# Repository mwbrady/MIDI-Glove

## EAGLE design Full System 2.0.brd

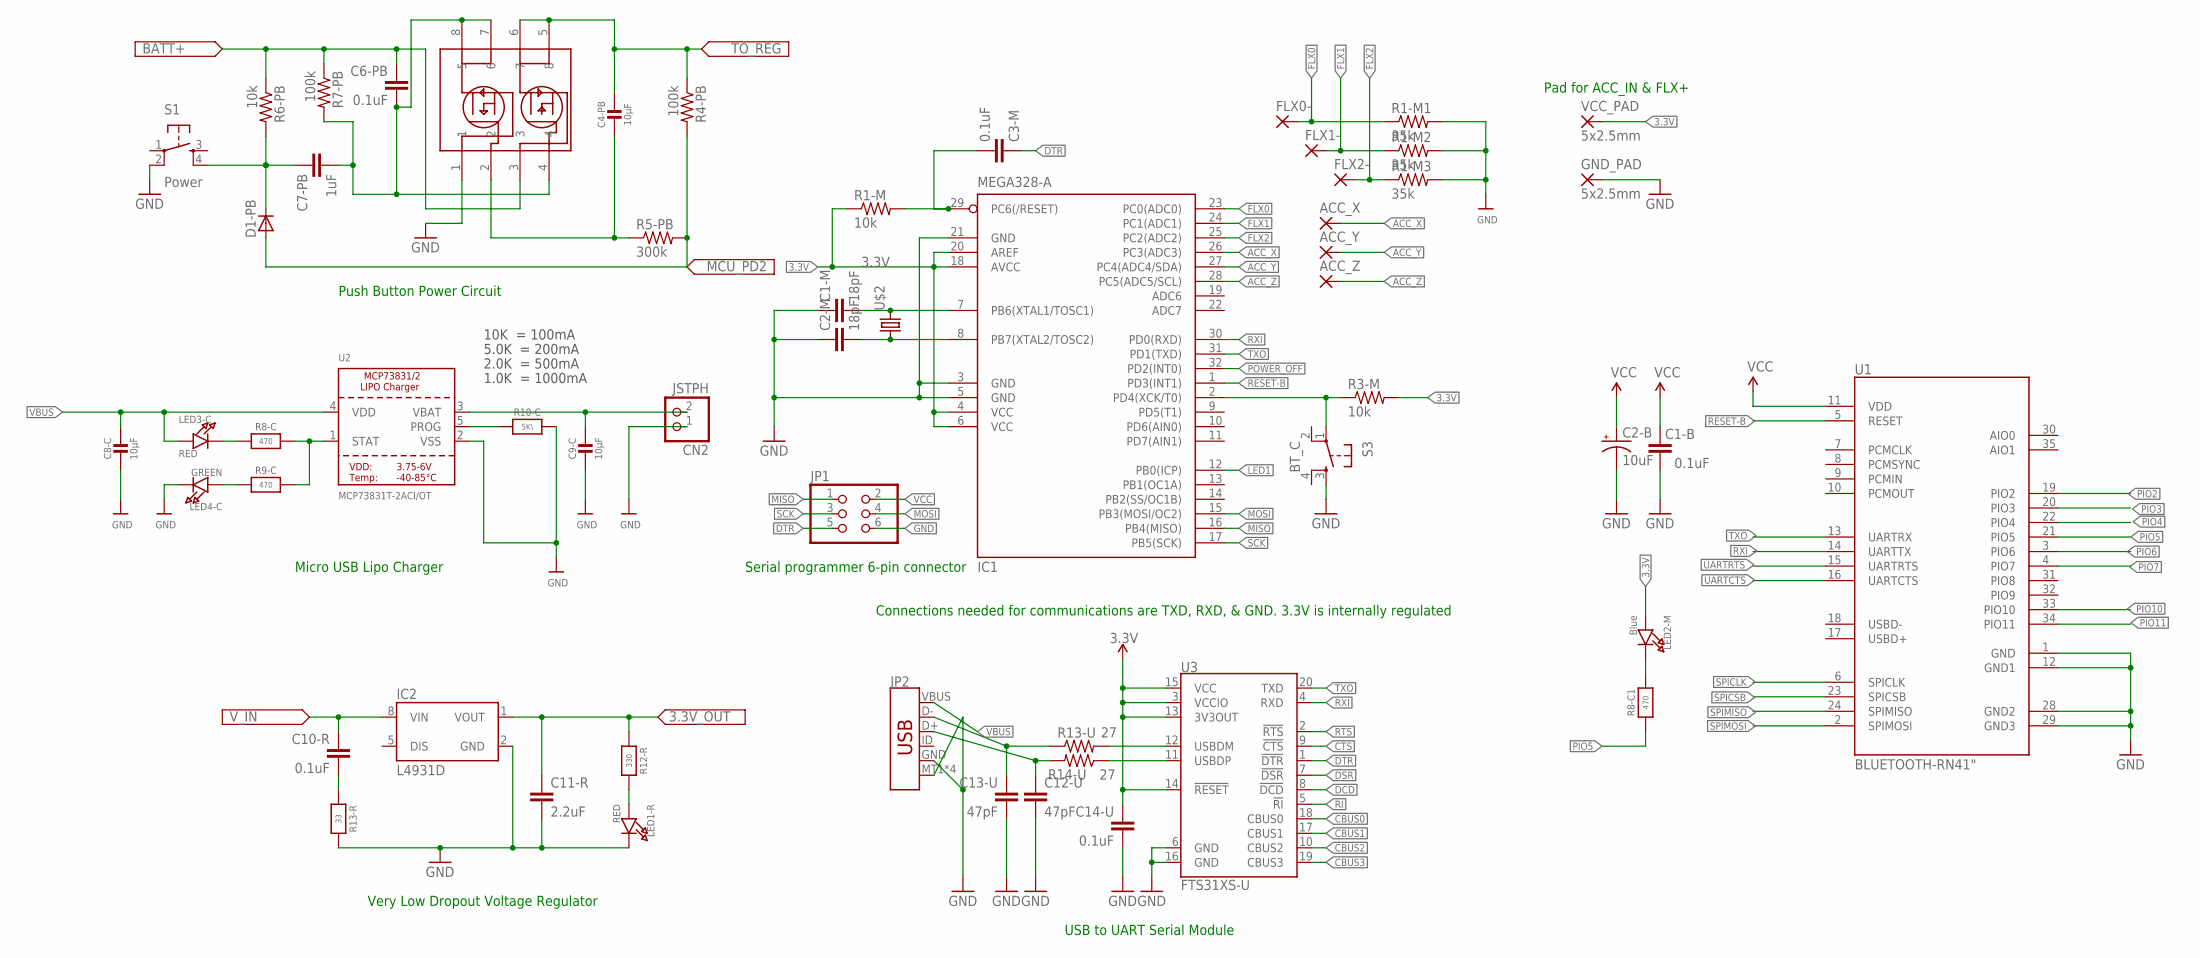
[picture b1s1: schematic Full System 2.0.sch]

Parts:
ACC_X: 1,6/0,8
ACC_Y: 1,6/0,8
ACC_Z: 1,6/0,8
C1-B, C3-M, C6-PB, C10-R, C14-U: 0.1uF; 0603-CAP
C1-M, C2-M: 18pF; C0603
C2-B: 10uF; EIA3216
C4-PB, C8-C, C9-C: 10µF; 0805-NO
C7-PB: 1uF; 0603-CAP
C11-R: 2.2uF; 0603-CAP
C12-U, C13-U: 47pF; 0603-CAP
CN2: JSTPH; JSTPH2
D1-PB: D-A1-C3; SOT23
FLX0-, FLX1-, FLX2-: 1,6/0,8
GND_PAD: 5x2.5mm; 5-2,5
IC1: MEGA328-A; TQFP32-08
IC2: L4931D; SO08
JP1: PINHD-2X3; 2X03
JP2: USB_MICRO-B_SMT; USB-MICROB
LED1-R, LED3-C: RED; CHIPLED_0805_NOOUTLINE
LED2-M: Blue; CHIPLED_0805_NOOUTLINE
LED4-C: GREEN; CHIPLED_0805_NOOUTLINE
R1-M, R3-M, R6-PB: 10k; R0805
R1-M1, R1-M2, R1-M3: 35k; R0805
R4-PB, R7-PB: 100k; R0805
R5-PB: 300k; R0805
R8-C, R8-C1, R9-C: 470; 0805-NO
R10-C: 5K\; 0805-NO
R12-R: 330; 0805-NO
R13-R: 33; 0805-NO
R13-U, R14-U: 27; 0603-RES
S1: Power; TACTILE_SWITCH_SMD
S3: BT_C; TACTILE_SWITCH_SMD
U1: BLUETOOTH-RN41"; RN41
U2: MCP73831T-2ACI/OT; SOT23-5
U3: FTS31XS-U; SSOP20_L
U$2: CRYSTAL
U$8: IRF7319PBF
VCC_PAD: 5x2.5mm; 5-2,5

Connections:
3.3V: C1-B.1, C2-B.A (+), C11-R.1, C14-U.1, IC1.4 (VCC), IC1.6 (VCC), IC1.18 (AVCC), IC1.20 (AREF), IC2.1 (VOUT), LED2-M.A, R1-M.1, R3-M.2, R12-R.1, U1.11 (VDD), U3.3 (VCCIO), U3.13 (3V3OUT), U3.14 (!RESET), U3.15 (VCC), VCC_PAD.1
ACC_X: ACC_X.1, IC1.26 (PC3(ADC3))
ACC_Y: ACC_Y.1, IC1.27 (PC4(ADC4/SDA))
ACC_Z: ACC_Z.1, IC1.28 (PC5(ADC5/SCL))
CBUS0: U3.18 (CBUS0)
CBUS3: U3.19 (CBUS3)
CTS: U3.9 (!CTS)
DCD: U3.8 (!DCD)
DSR: U3.7 (!DSR)
DTR: C3-M.1, JP1.5, U3.1 (!DTR)
FLX0: FLX0-.1, IC1.23 (PC0(ADC0)), R1-M1.1
FLX1: FLX1-.1, IC1.24 (PC1(ADC1)), R1-M2.1
FLX2: FLX2-.1, IC1.25 (PC2(ADC2)), R1-M3.1
GND: C1-B.2, C1-M.1, C2-B.C (-), C2-M.1, C8-C.2, C9-C.2, C11-R.2, C12-U.2, C13-U.2, C14-U.2, CN2.1, GND_PAD.1, IC1.3 (GND), IC1.5 (GND), IC1.21 (GND), IC2.2 (GND), JP1.6, JP2.GND, JP2.MT1 (SHIELD), JP2.MT2 (SHIELD), JP2.P$1 (SHIELD), JP2.P$2 (SHIELD), LED1-R.C, LED4-C.C, R1-M1.2, R1-M2.2, R1-M3.2, R10-C.2, R13-R.2, S1.2, S3.3, U1.1 (GND), U1.12 (GND1), U1.28 (GND2), U1.29 (GND3), U2.2 (VSS), U3.6 (GND), U3.16 (GND), U$8.1
LED1: IC1.12 (PB0(ICP))
MISO: IC1.16 (PB4(MISO)), JP1.1
MOSI: IC1.15 (PB3(MOSI/OC2)), JP1.4
unnamed: R13-U.2, U3.12 (USBDM)
unnamed: C1-M.2, IC1.7 (PB6(XTAL1/TOSC1)), U$2.P$2 (2)
unnamed: C2-M.2, IC1.8 (PB7(XTAL2/TOSC2)), U$2.P$1 (1)
unnamed: C6-PB.2, C7-PB.2, R7-PB.2, U$8.4, U$8.7 (6), U$8.8 (5)
unnamed: C7-PB.1, D1-PB.3 (C), R6-PB.2, S1.4
unnamed: IC1.2 (PD4(XCK/T0)), R3-M.1, S3.1
unnamed: LED1-R.A, R12-R.2
unnamed: C10-R.2, R13-R.1
unnamed: C4-PB.2, R5-PB.1, U$8.2
unnamed: LED2-M.C, R8-C1.2
unnamed: R14-U.1, U3.11 (USBDP)
unnamed: C12-U.1, JP2.D+, R14-U.2
unnamed: LED3-C.C, R8-C.1
unnamed: R8-C.2, R9-C.2, U2.1 (STAT)
unnamed: R10-C.1, U2.5 (PROG)
unnamed: LED4-C.A, R9-C.1
unnamed: C13-U.1, JP2.D-, R13-U.1
PIO2: U1.19 (PIO2)
PIO3: U1.20 (PIO3)
PIO4: U1.22 (PIO4)
PIO5: R8-C1.1, U1.21 (PIO5)
PIO6: U1.3 (PIO6)
PIO7: U1.4 (PIO7)
PIO10: U1.33 (PIO10)
PIO11: U1.34 (PIO11)
POWER_OFF: D1-PB.1 (A), IC1.32 (PD2(INT0)), R4-PB.2, R5-PB.2
RESET: C3-M.2, IC1.29 (PC6(/RESET)), R1-M.2
RESET-B: IC1.1 (PD3(INT1)), U1.5 (RESET)
RI: U3.5 (!RI)
RTS: U3.2 (!RTS)
RXI: IC1.30 (PD0(RXD)), U1.14 (UARTTX), U3.4 (RXD)
SCK: IC1.17 (PB5(SCK)), JP1.3
SPICLK: U1.6 (SPICLK)
SPICSB: U1.23 (SPICSB)
SPIMISO: U1.24 (SPIMISO)
SPIMOSI: U1.2 (SPIMOSI)
TXO: IC1.31 (PD1(TXD)), U1.13 (UARTRX), U3.20 (TXD)
UARTCTS: U1.16 (UARTCTS)
UARTRTS: U1.15 (UARTRTS)
VBAT: C6-PB.1, C9-C.1, CN2.2, R6-PB.1, R7-PB.1, U2.3 (VBAT), U$8.3
VBUS: C8-C.1, JP2.VBUS, LED3-C.A, U2.4 (VDD)
VCC: JP1.2
V_IN: C4-PB.1, C10-R.1, IC2.8 (VIN), R4-PB.1, U$8.5 (8), U$8.6 (7)

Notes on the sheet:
Serial programmer 6-pin connector
Pad for ACC_IN & FLX+
Connections needed for communications are TXD, RXD, & GND. 3.3V is internally regulated
10K = 100mA
5.0K = 200mA
2.0K = 500mA
1.0K = 1000mA
USB to UART Serial Module
Very Low Dropout Voltage Regulator
Micro USB Lipo Charger
Push Button Power Circuit

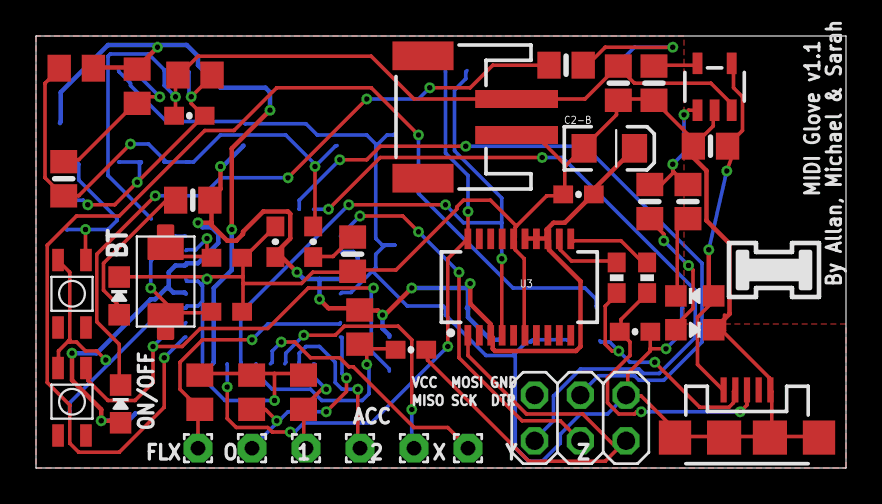
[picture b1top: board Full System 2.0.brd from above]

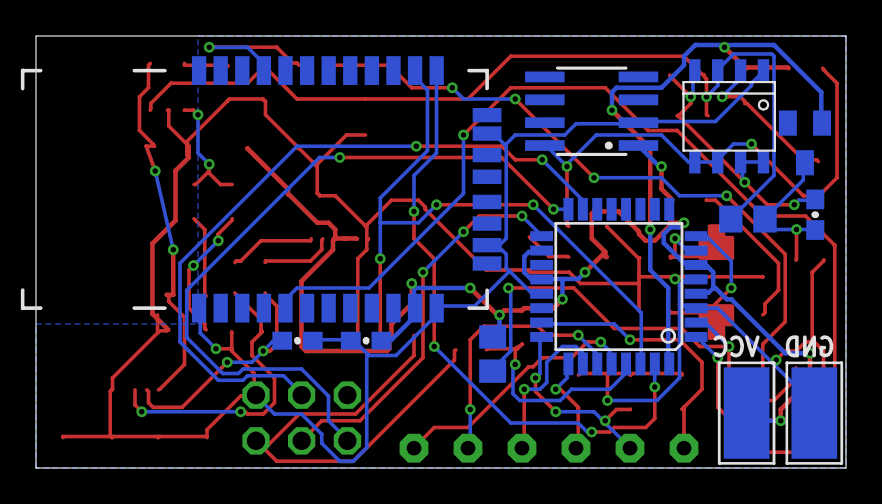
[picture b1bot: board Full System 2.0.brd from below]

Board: 2 copper layers, 45.0 x 24.0 mm, 57 parts (12 on the bottom side), 38 nets.

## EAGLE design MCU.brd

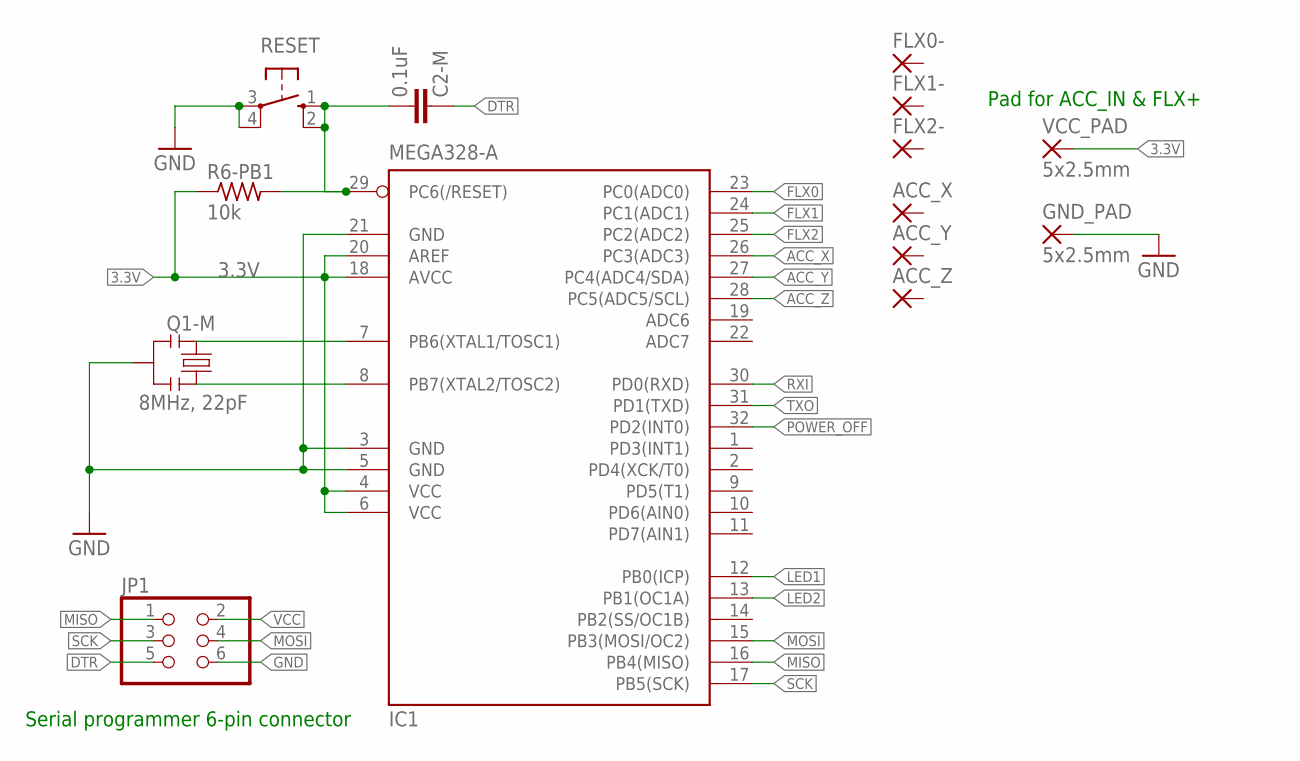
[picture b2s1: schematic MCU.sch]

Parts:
ACC_X: 1,6/0,8
ACC_Y: 1,6/0,8
ACC_Z: 1,6/0,8
C2-M: 0.1uF; 0603-CAP
FLX0-, FLX1-, FLX2-: 1,6/0,8
GND_PAD: 5x2.5mm; 5-2,5
IC1: MEGA328-A; TQFP32-08
JP1: PINHD-2X3; 2X03
Q1-M: 8MHz, 22pF; RESONATOR-SMD-1:1
R6-PB1: 10k; R0805
RESET: 10-XX; B3F-10XX
VCC_PAD: 5x2.5mm; 5-2,5

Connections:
3.3V: IC1.4 (VCC), IC1.6 (VCC), IC1.18 (AVCC), IC1.20 (AREF), R6-PB1.1, VCC_PAD.1
ACC_X: IC1.26 (PC3(ADC3))
ACC_Y: IC1.27 (PC4(ADC4/SDA))
ACC_Z: IC1.28 (PC5(ADC5/SCL))
DTR: C2-M.2, JP1.5
FLX0: IC1.23 (PC0(ADC0))
FLX2: IC1.25 (PC2(ADC2))
FLX!: IC1.24 (PC1(ADC1))
GND: GND_PAD.1, IC1.3 (GND), IC1.5 (GND), IC1.21 (GND), JP1.6, Q1-M.2, RESET.3, RESET.4 (P1)
MISO: IC1.16 (PB4(MISO)), JP1.1
MOSI: IC1.15 (PB3(MOSI/OC2)), JP1.4
unnamed: C2-M.1, IC1.29 (PC6(/RESET)), R6-PB1.2, RESET.1 (S), RESET.2 (S1)
unnamed: IC1.7 (PB6(XTAL1/TOSC1)), Q1-M.1
unnamed: IC1.8 (PB7(XTAL2/TOSC2)), Q1-M.3
POWER_OFF: IC1.32 (PD2(INT0))
RXI: IC1.30 (PD0(RXD))
SCK: IC1.17 (PB5(SCK)), JP1.3
TXO: IC1.31 (PD1(TXD))
VCC: JP1.2

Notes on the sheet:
Serial programmer 6-pin connector
Pad for ACC_IN & FLX+

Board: 2 copper layers, 14 parts (0 on the bottom side), 9 nets, no tracks yet.

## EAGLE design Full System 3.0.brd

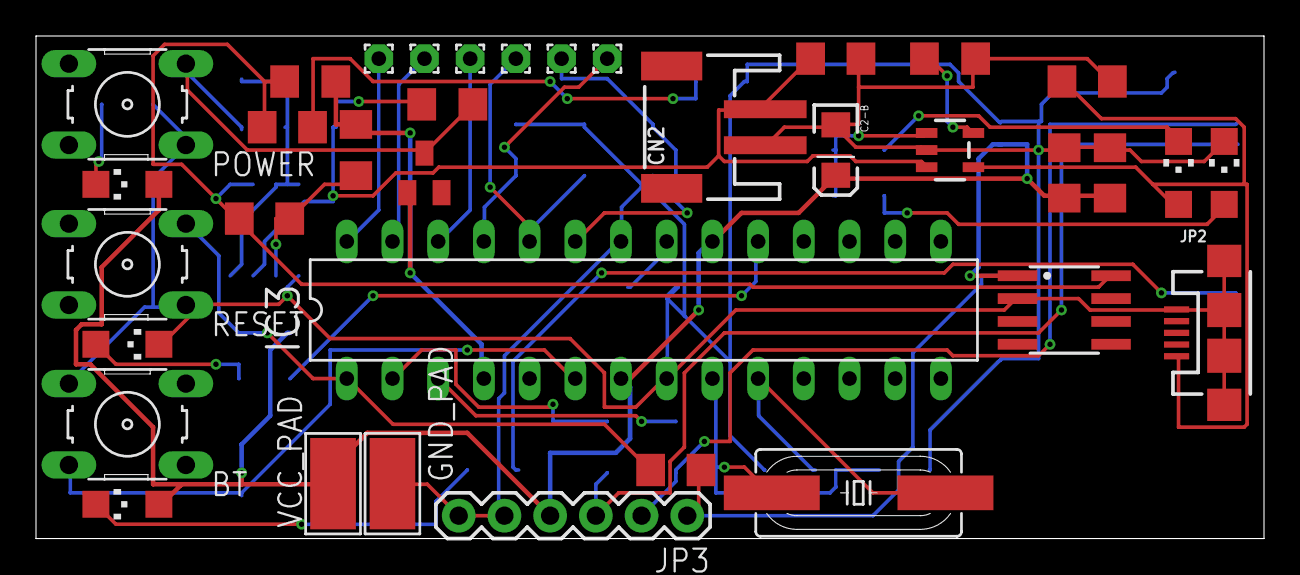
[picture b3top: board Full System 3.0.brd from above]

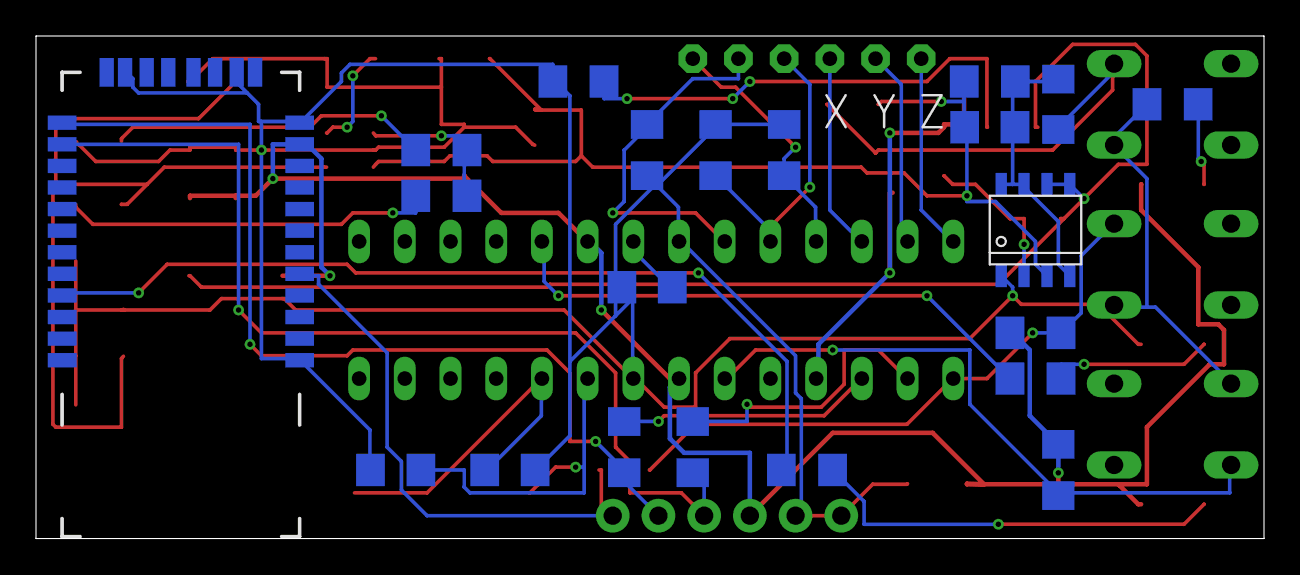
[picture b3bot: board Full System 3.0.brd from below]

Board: 2 copper layers, 68.2 x 27.9 mm, 57 parts (21 on the bottom side), 35 nets.

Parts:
ACC_X: 1,6/0,8
ACC_Y: 1,6/0,8
ACC_Z: 1,6/0,8
BT: B3F-10XX
C1, C1-B, C2, C6-PB, C10-R: 0.1uF; C1206
C1-M, C2-M: 18pF; C1206
C2-B: 10uF; EIA3216
C4-PB, C8-C, C9-C: 10µF; C1206
C7-PB: 1uF; C1206
C11-R: 2.2uF; C1206
CN2: JSTPH; JSTPH2
D1-PB: SOT23
D3: Green; CHIPLED_1206
FLX0-, FLX1-, FLX2-: 1,6/0,8
GND_PAD: 5x2.5mm; 5-2,5
IC2: L4931D; SO08
IC3: MEGA8-P; DIL28-3
JP2: USB-MICROB
JP3: FTDI Basic; 1X06
LED1: Red; CHIPLED_1206
LED2-M: Blue; CHIPLED_1206
LED3-C: RED; CHIPLED_1206
LED4-C: GREEN; CHIPLED_1206
POWER: B3F-10XX
R1-M1, R1-M2, R1-M3: 35k; R1206
R2: 10K; R1206
R3-M, R4-M, R11: 1k; R1206
R4-PB, R7-PB: 100k; R1206
R5-M, R6-PB: 10k; R1206
R5-PB: 300k; R1206
R6: 330; R1206
R8-C, R8-C1, R9-C: 470; R1206
R10-C: 5K\; R1206
R13-R: 33; R1206
RESET: B3F-10XX
U1: BLUETOOTH-RN41"; RN41
U2: MCP73831T-2ACI/OT; SOT23-5
U$2: HC49UP
U$8: IRF7319PBF
VCC_PAD: 5x2.5mm; 5-2,5

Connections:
3.3V: C1-B.1, C2-B.A, C11-R.1, IC2.1, IC3.7, IC3.20, JP3.4, LED1.A, LED2-M.A, R2.2, R5-M.2, U1.11, VCC_PAD.1
ACC_X: ACC_X.1, IC3.26
ACC_Y: ACC_Y.1, IC3.27
ACC_Z: ACC_Z.1, IC3.28
DTR: C2.2, JP3.1, U1.5
FLX0: FLX0-.1, IC3.23, R1-M1.1
FLX1: FLX1-.1, IC3.24, R1-M2.1
FLX2: FLX2-.1, IC3.25, R1-M3.1
GND: BT.1, C1.1, C1-B.2, C1-M.1, C2-B.C, C2-M.1, C8-C.2, C9-C.2, C11-R.2, CN2.1, D3.C, GND_PAD.1, IC2.2, IC3.8, IC3.22, JP2.GND, JP2.MT1, JP2.MT2, JP2.P$1, JP2.P$2, JP3.5, JP3.6, LED4-C.C, POWER.4, R1-M1.2, R1-M2.2, R1-M3.2, R10-C.2, R11.1, R13-R.2, RESET.4, U1.1, U1.12, U1.28, U1.29, U2.2, U$8.1
unnamed: C1-M.2, IC3.9, U$2.2
unnamed: C2-M.2, IC3.10, U$2.1
unnamed: C6-PB.2, C7-PB.2, R7-PB.2, U$8.4, U$8.7, U$8.8
unnamed: C7-PB.1, D1-PB.3, POWER.2, R6-PB.2
unnamed: BT.3, IC3.6, R5-M.1
unnamed: LED1.C, R11.2
unnamed: C10-R.2, R13-R.1
unnamed: C4-PB.2, R5-PB.1, U$8.2
unnamed: LED2-M.C, R8-C1.2
unnamed: D3.A, R6.2
unnamed: R8-C1.1, U1.21
unnamed: C1.2, IC3.21
unnamed: LED3-C.C, R8-C.1
unnamed: R8-C.2, R9-C.2, U2.1
unnamed: R10-C.1, U2.5
unnamed: LED4-C.A, R9-C.1
unnamed: IC3.2, R3-M.1
unnamed: IC3.3, R4-M.1
POWER_OFF: D1-PB.1, IC3.4, R4-PB.2, R5-PB.2
RESET: C2.1, IC3.1, R2.1, RESET.2
RXI: JP3.3, R3-M.2, U1.14
SCK: IC3.19, R6.1
TXO: JP3.2, R4-M.2, U1.13
VBAT: C6-PB.1, C9-C.1, CN2.2, R6-PB.1, R7-PB.1, U2.3, U$8.3
VBUS: C8-C.1, JP2.VBUS, LED3-C.A, U2.4
V_IN: C4-PB.1, C10-R.1, IC2.8, R4-PB.1, U$8.5, U$8.6

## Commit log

2018-03-05 Add files via upload
    Voltage Divider Circuits

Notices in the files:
parts and their libraries:
SparkFun-Capacitors: Licensing: CC v3.0 Share-Alike You are welcome to use this library for commercial purposes.
microbuilder: This work is placed in the public domain, and may be freely used for commercial and non-commercial work with the following conditions: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
